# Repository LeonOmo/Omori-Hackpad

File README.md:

# Hackpad
A custom designed macro controller featuring MX switches, custom keycaps, an OLED display, a rotary knob, and engraved Omori artwork. Built for Hack Club Stardance.

Features
 - Brain: ESP32 WROOM 32
 - Controls: 3x MX Mechanical Switches, 1x Rotary Encoder
 - Display: OLED screen
 - Case: Designed in Onshape

Preview

Schematic (Its my first so its abit messy)

PCB

3D Model

I Made three push buttons (GP0, GP1, GP10) for custom keypresses and a rotary encoder (GP3, GP5) for volume control. It also has an OLED display (GP7, GP8) to show Volume.

Status
- [x] Creating Schematic
- [x] Creating PCB 
- [x] 3D Modeling & Enclosure Design (Onshape)
- [x] Firmware Development

Im sorry for not reading it properly

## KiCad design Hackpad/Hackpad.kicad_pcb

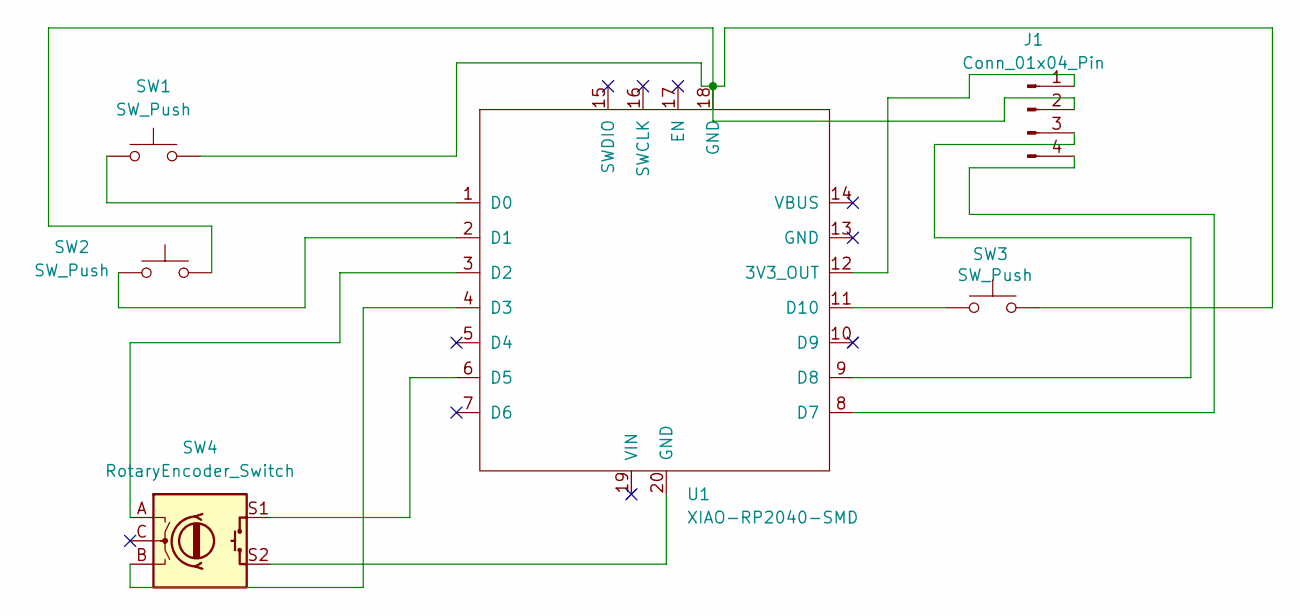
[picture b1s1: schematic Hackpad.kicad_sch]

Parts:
J1: Conn_01x04_Pin; FanPinHeader_1x04_P2.54mm_Vertical
SW1, SW2, SW3: SW_Push; SW_Cherry_MX_1.00u_PCB
SW4: RotaryEncoder_Switch; RotaryEncoder_Alps_EC11E-Switch_Vertical_H20mm
U1: XIAO-RP2040-SMD

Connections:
unnamed: J1.1, U1.12 (3V3_OUT)
unnamed: J1.2, SW1.2, SW2.2, SW3.2, U1.18 (GND)
unnamed: J1.3, U1.9 (D8)
unnamed: J1.4, U1.8 (D7)
unnamed: SW4.S2, U1.20 (GND)
unnamed: SW1.1, U1.1 (D0)
unnamed: SW2.1, U1.2 (D1)
unnamed: SW4.A, U1.3 (D2)
unnamed: SW4.B, U1.4 (D3)
unnamed: SW4.S1, U1.6 (D5)
unnamed: SW3.1, U1.11 (D10)

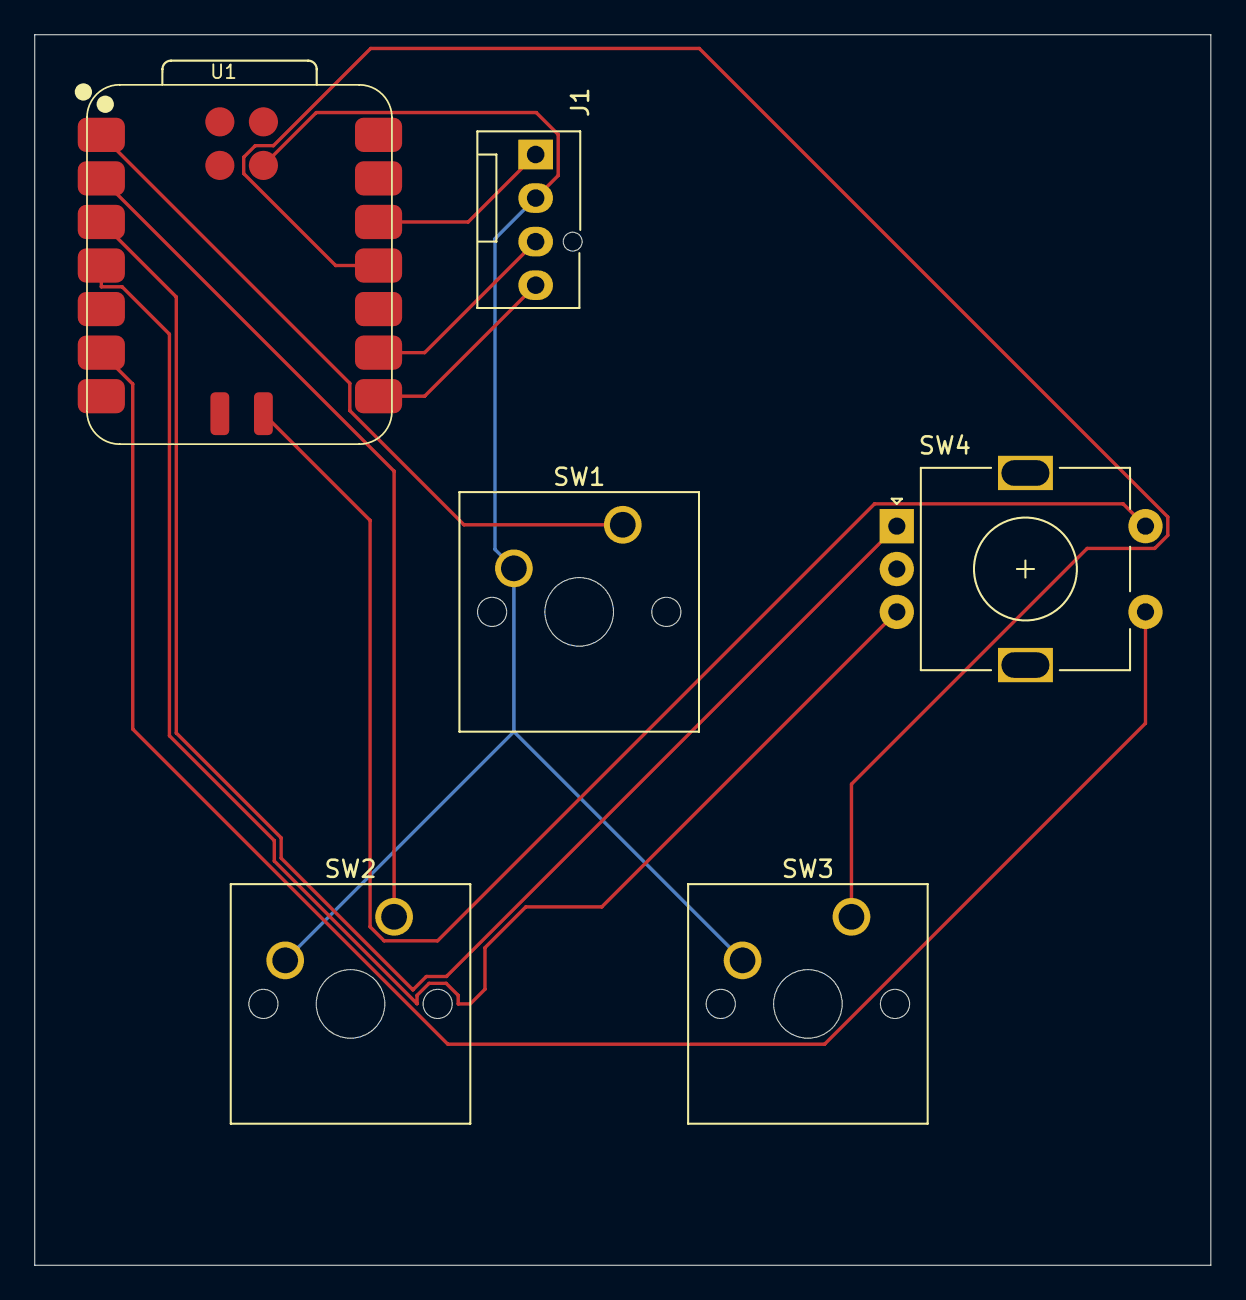
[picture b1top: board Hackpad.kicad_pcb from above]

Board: 2 copper layers, 68.6 x 71.8 mm, 6 parts (0 on the bottom side), 11 nets.
